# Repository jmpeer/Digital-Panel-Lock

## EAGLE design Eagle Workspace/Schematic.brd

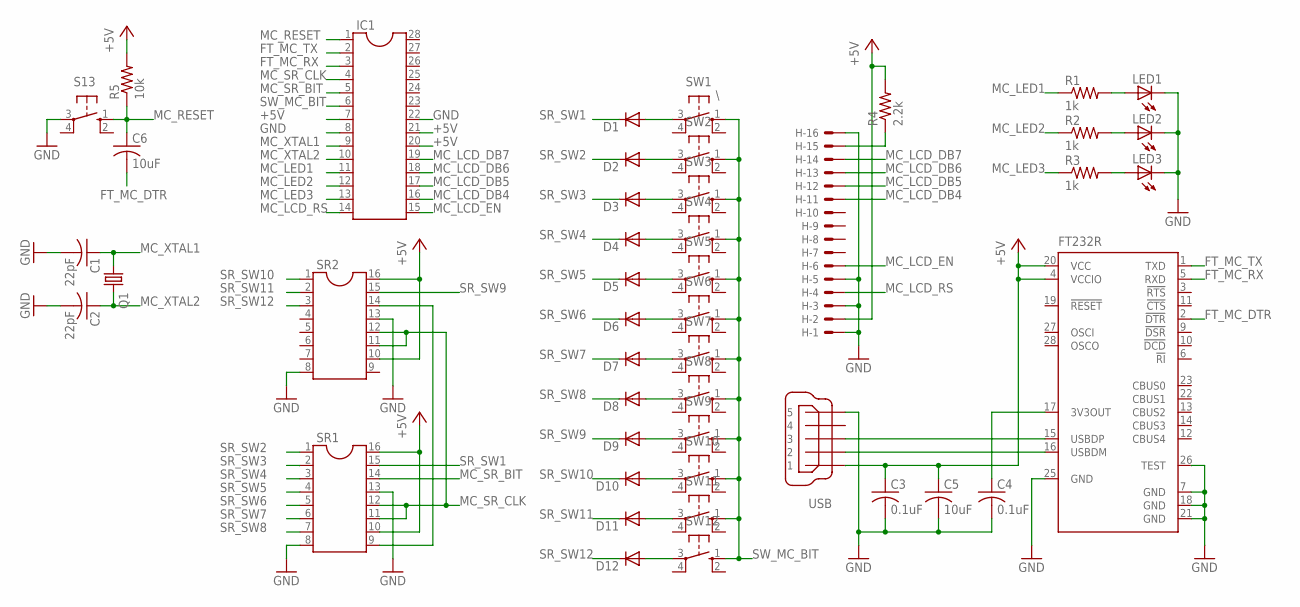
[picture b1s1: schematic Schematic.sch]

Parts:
C1, C2: 22pF; C025-024X044
C3, C4: 0.1uF; C025-024X044
C5, C6: 10uF; C025-024X044
D1, D2, D3, D4, D5, D6, D7, D8, D9, D10, D11, D12: DIODE-DO35-10; DO35-10
FT232R: FT232RL; SSOP28
H: C-GRID-16-70543; 70543-16
IC1: DIL28-3
LED1, LED2, LED3: LED3MM
Q1: CRYSTALHC49U-V; HC49U-V
R1, R2, R3: 1k; 0204V
R4: 2.2k; 0204V
R5: 10k; 0204V
S13: 10-XX; B3F-10XX
SR1, SR2: DIL16
SW1: \; B3F-10XX
SW2, SW3, SW4, SW5, SW6, SW7, SW8, SW9, SW10, SW11, SW12: 10-XX; B3F-10XX
USB: MINI-USB_SHIELD5P2-32005-601; 32005-601

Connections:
+5V: C3.1, C5.1, FT232R.4 (VCCIO), FT232R.20 (VCC), H.2, IC1.7, IC1.20, IC1.21, R4.2, R5.2, SR1.10, SR1.16, SR2.10, SR2.16, USB.1
FT_MC_DTR: C6.2, FT232R.2 (!DTR)
FT_MC_RX: FT232R.5 (RXD), IC1.3
FT_MC_TX: FT232R.1 (TXD), IC1.2
GND: C1.2, C2.2, C3.2, C4.2, C5.2, FT232R.7 (GND), FT232R.18 (GND), FT232R.21 (GND), FT232R.25 (GND), FT232R.26 (TEST), H.1, H.3, H.5, H.16, IC1.8, IC1.22, LED1.K (C), LED2.K (C), LED3.K (C), S13.3, SR1.8, SR1.13, SR2.8, SR2.13, USB.5
IDK: SR1.9, SR2.14
MC_LCD_DB4: H.11, IC1.16
MC_LCD_DB5: H.12, IC1.17
MC_LCD_DB6: H.13, IC1.18
MC_LCD_DB7: H.14, IC1.19
MC_LCD_EN: H.6, IC1.15
MC_LCD_RS: H.4, IC1.14
MC_LED1: IC1.11, R1.1
MC_LED2: IC1.12, R2.1
MC_LED3: IC1.13, R3.1
MC_RESET: C6.1, IC1.1, R5.1, S13.1 (S)
MC_SR_BIT: IC1.5, SR1.14
MC_SR_CLK: IC1.4, SR1.11, SR1.12, SR2.11, SR2.12
MC_XTAL1: C1.1, IC1.9, Q1.1
MC_XTAL2: C2.1, IC1.10, Q1.2
unnamed: D12.A, SW12.3
unnamed: D11.A, SW11.3
unnamed: D10.A, SW10.3
unnamed: D9.A, SW9.3
unnamed: D8.A, SW8.3
unnamed: D7.A, SW7.3
unnamed: D6.A, SW6.3
unnamed: D5.A, SW5.3
unnamed: D4.A, SW4.3
unnamed: D1.A, SW1.3
unnamed: D2.A, SW2.3
unnamed: D3.A, SW3.3
unnamed: FT232R.15 (USBDP), USB.3
unnamed: FT232R.16 (USBDM), USB.2
unnamed: LED1.A, R1.2
unnamed: LED2.A, R2.2
unnamed: H.15, R4.1
unnamed: LED3.A, R3.2
unnamed: C4.1, FT232R.17 (3V3OUT)
SR_SW1: D1.C, SR1.15
SR_SW2: D2.C, SR1.1
SR_SW3: D3.C, SR1.2
SR_SW4: D4.C, SR1.3
SR_SW5: D5.C, SR1.4
SR_SW6: D6.C, SR1.5
SR_SW7: D7.C, SR1.6
SR_SW8: D8.C, SR1.7
SR_SW9: D9.C, SR2.15
SR_SW10: D10.C, SR2.1
SR_SW11: D11.C, SR2.2
SR_SW12: D12.C, SR2.3
SW_MC_BIT: IC1.6, SW1.1 (S), SW2.1 (S), SW3.1 (S), SW4.1 (S), SW5.1 (S), SW6.1 (S), SW7.1 (S), SW8.1 (S), SW9.1 (S), SW10.1 (S), SW11.1 (S), SW12.1 (S)

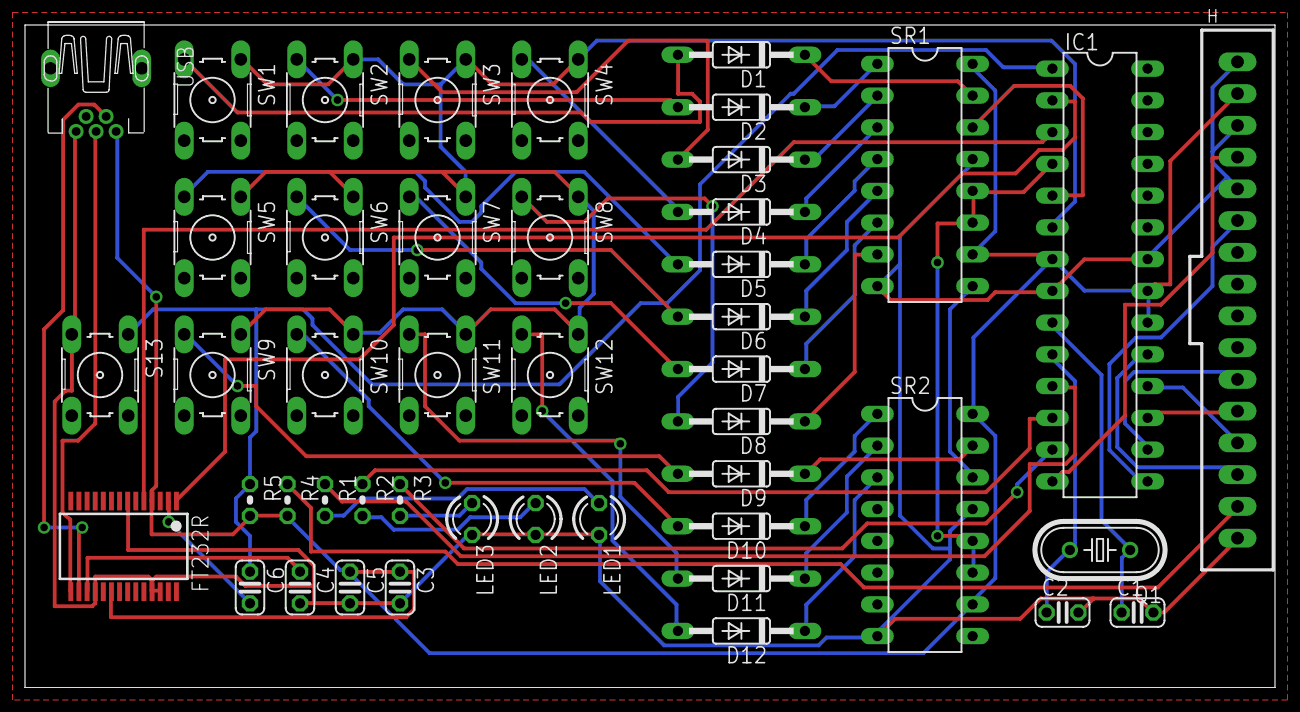
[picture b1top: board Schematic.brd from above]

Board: 2 copper layers, 100.0 x 53.0 mm, 46 parts (0 on the bottom side), 52 nets.
